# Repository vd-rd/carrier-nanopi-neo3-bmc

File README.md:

# NanoPi Neo 3 Carrier board

This board is designed to enhance the FriendlyElec NanoPi Neo 3 board with features suitable for a "server" style deployment. It uses a ESP32 as a BMC.

Features provided:
 - RTC clock 
 - Wired Ethernet interface
 - Gated power supply

## Motivation

Most SBC platforms lack the features needed for a rack style deployment where you can power cycle the board or get a remote console to debug what went wrong.
The ESP32 uC is fairly popular, but the reason behind selecting it to act as a BMC is that is one of the cheapest uCs equipped with a Ethernet PHY.

## Hardware overview
 (Diagram)

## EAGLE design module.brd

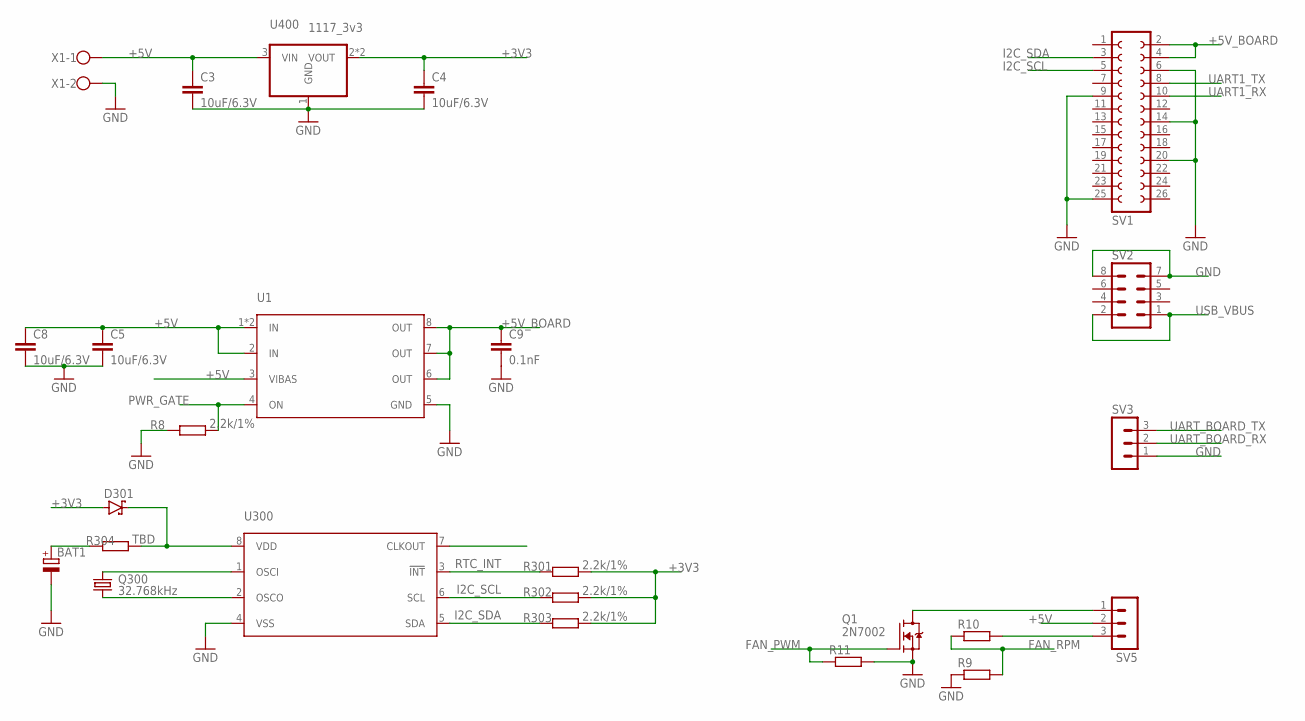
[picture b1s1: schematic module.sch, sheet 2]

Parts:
BAT1: DCK-3R3E224U-E; 621
C3, C4: 10uF/6.3V; C1206
C5, C8: 10uF/6.3V; C0603
C9: 0.1nF; C0603
D301: NSR0320; SOD323
Q1: 2N7002; SOT95P240X110-3
Q300: 32.768kHz; 3215
R8, R301, R302, R303: 2.2k/1%; R0603
R9, R10, R11: R-EU_R0603; R0603
R304: TBD; R0603
SV1: FE13-2
SV2: MA04-2
SV3: MA03-1FEMALE; MA03-1
SV5: MA03-1
U1: DML10M8LDS; SON65P300X300X80-9T160X240N
U300: PCF85063ATT; SOP65P490X110-8N
U400: 1117_3v3; SOT230P700X180-4
X1: W237-102; EBBA

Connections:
+3V3: C4.1, D301.A, R301.2, R302.2, R303.2, U400.2 (VOUT), U400.4 (VOUT); also elsewhere on the board
+5V: C3.1, C5.1, C8.1, SV5.2, U1.1 (IN), U1.2 (IN), U1.3 (VIBAS), U1.9 (IN), U400.3 (VIN), X1.1
+5V_BOARD: C9.1, SV1.2, SV1.4, U1.6 (OUT), U1.7 (OUT), U1.8 (OUT)
FAN_PWM: Q1.1 (G), R11.1; also elsewhere on the board
FAN_RPM: R9.2, R10.1; also elsewhere on the board
GND: BAT1.-, C3.2, C4.2, C5.2, C8.2, C9.2, Q1.2 (S), R8.1, R9.1, R11.2, SV1.6, SV1.9, SV1.14, SV1.20, SV1.25, SV2.7, SV2.8, SV3.1, U1.5 (GND), U300.4 (VSS), U400.1 (GND), X1.2; also elsewhere on the board
I2C_SCL: R302.1, SV1.5, U300.6 (SCL); also elsewhere on the board
I2C_SDA: R303.1, SV1.3, U300.5 (SDA); also elsewhere on the board
unnamed: Q1.3 (D), SV5.1
unnamed: R10.2, SV5.3
unnamed: Q300.1, U300.2 (OSCO)
unnamed: Q300.2, U300.1 (OSCI)
unnamed: BAT1.+, R304.1
unnamed: D301.K (C), R304.2, U300.8 (VDD)
PWR_GATE: R8.2, U1.4 (ON); also elsewhere on the board
RTC_INT: R301.1, U300.3 (!INT)
UART1_RX: SV1.10
UART1_TX: SV1.8
UART_BOARD_RX: SV3.2; also elsewhere on the board
UART_BOARD_TX: SV3.3; also elsewhere on the board
USB_VBUS: SV2.1, SV2.2

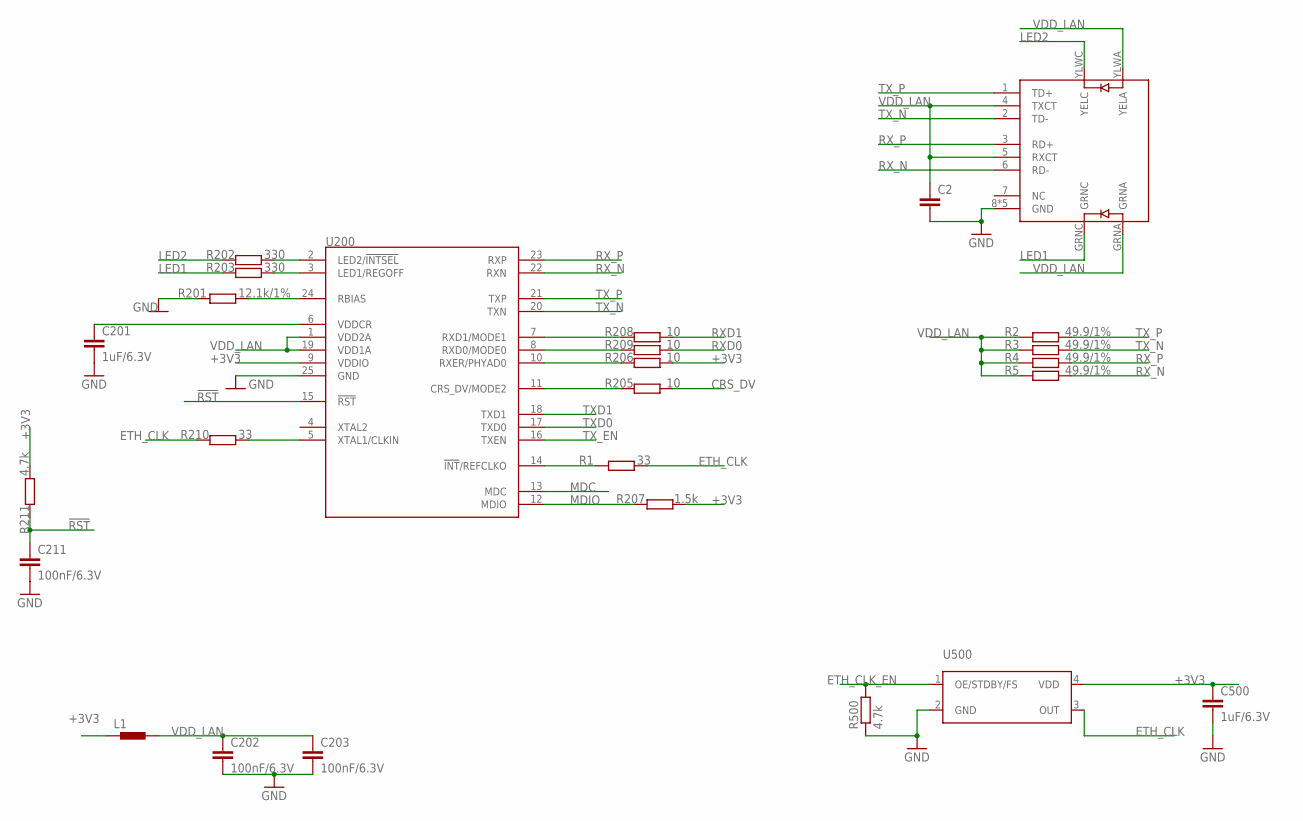
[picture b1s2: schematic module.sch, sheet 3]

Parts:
C2: C-EUC0603; C0603
C201, C500: 1uF/6.3V; C0603
C202, C203, C211: 100nF/6.3V; C0603
J1: ARJM11X1009XXXXX; LAYOUT1-HORIZ-LEDS
L1: FER-0603; FER0603
R1, R210: 33; R0603
R2, R3, R4, R5: 49.9/1%; R0603
R201: 12.1k/1%; R0603
R202, R203: 330; R0603
R205, R206, R208, R209: 10; R0603
R207: 1.5k; R0603
R211, R500: 4.7k; R0603
U200: LAN8720A; QFN50P400X400X100-25T250N
U500: DSC61XXC; DIODFN250X200X89-4N

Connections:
!RST: C211.1, R211.1, U200.15 (!RST)
+3V3: C500.1, L1.1, R206.2, R207.2, R211.2, U200.9 (VDDIO), U500.4 (VDD); also elsewhere on the board
CRS_DV: R205.2; also elsewhere on the board
ETH_CLK: R1.2, R210.1, U500.3 (OUT); also elsewhere on the board
ETH_CLK_EN: R500.2, U500.1 (OE/STDBY/FS); also elsewhere on the board
GND: C2.2, C201.2, C202.2, C203.2, C211.2, C500.2, J1.8 (GND), J1.P$1 (GND), J1.P$2 (GND), J1.P$3 (GND), J1.P$4 (GND), R201.1, R500.1, U200.25 (GND), U500.2 (GND); also elsewhere on the board
LED1: J1.GRNC, R203.1
LED2: J1.YLWC (YELC), R202.1
MDC: U200.13 (MDC); also elsewhere on the board
MDIO: R207.1, U200.12 (MDIO); also elsewhere on the board
unnamed: R208.1, U200.7 (RXD1/MODE1)
unnamed: R210.2, U200.5 (XTAL1/CLKIN)
unnamed: C201.1, U200.6 (VDDCR)
unnamed: R202.2, U200.2 (LED2/!INTSEL)
unnamed: R203.2, U200.3 (LED1/REGOFF)
unnamed: R209.1, U200.8 (RXD0/MODE0)
unnamed: R201.2, U200.24 (RBIAS)
unnamed: R206.1, U200.10 (RXER/PHYAD0)
unnamed: R205.1, U200.11 (CRS_DV/MODE2)
unnamed: R1.1, U200.14 (!INT!/REFCLKO)
RXD0: R209.2; also elsewhere on the board
RXD1: R208.2; also elsewhere on the board
RX_N: J1.6 (RD-), R5.2, U200.22 (RXN)
RX_P: J1.3 (RD+), R4.2, U200.23 (RXP)
TXD0: U200.17 (TXD0); also elsewhere on the board
TXD1: U200.18 (TXD1); also elsewhere on the board
TX_EN: U200.16 (TXEN); also elsewhere on the board
TX_N: J1.2 (TD-), R3.2, U200.20 (TXN)
TX_P: J1.1 (TD+), R2.2, U200.21 (TXP)
VDD_LAN: C2.1, C202.1, C203.1, J1.4 (TXCT), J1.5 (RXCT), J1.GRNA, J1.YLWA (YELA), L1.2, R2.1, R3.1, R4.1, R5.1, U200.1 (VDD2A), U200.19 (VDD1A)

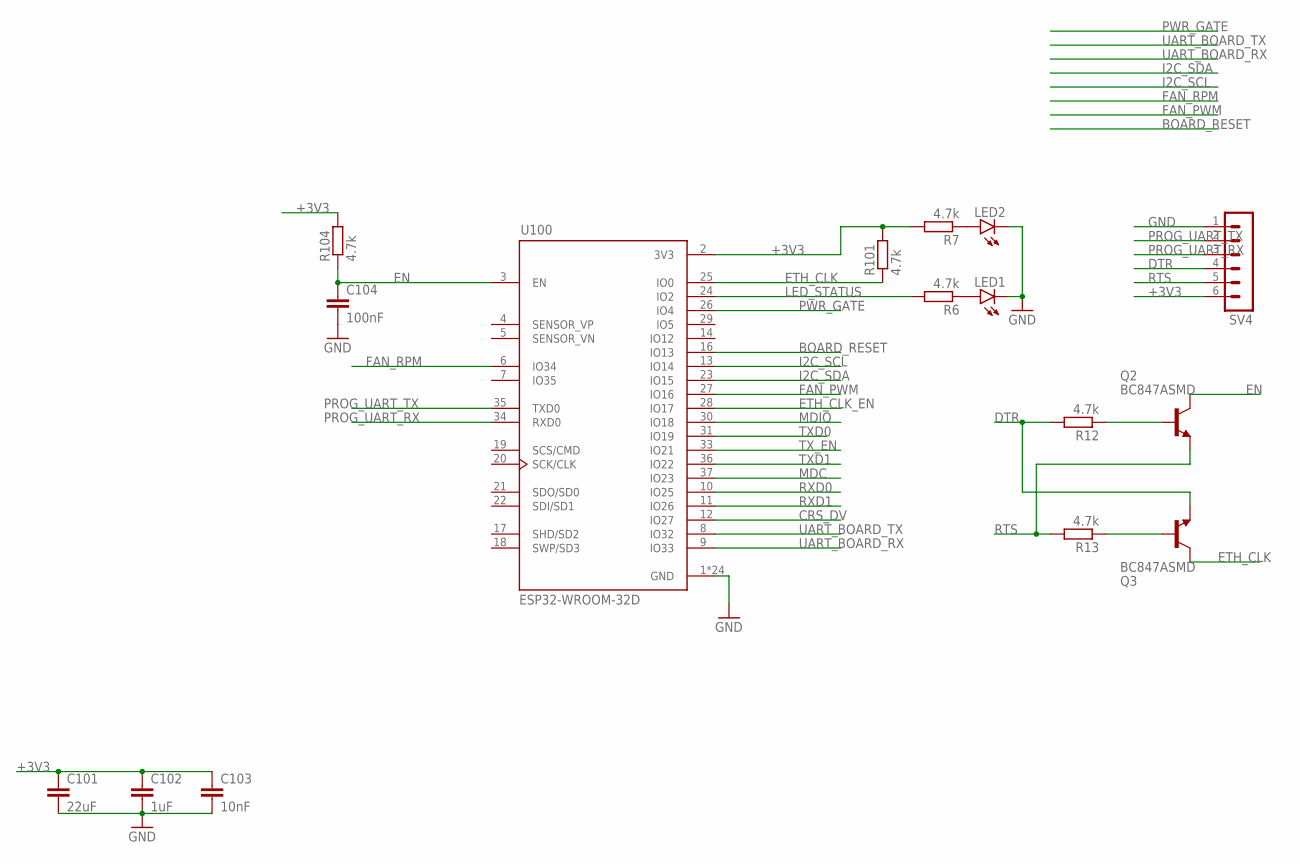
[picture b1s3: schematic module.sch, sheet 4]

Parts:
C101: 22uF; C1206
C102: 1uF; C0603
C103: 10nF; C0603
C104: 100nF; C0603
LED1, LED2: LEDCHIP-LED0805; CHIP-LED0805
Q2, Q3: BC847ASMD; SOT23
R6, R7, R12, R13, R101, R104: 4.7k; R0603
SV4: CONN-1X6; MA06-1
U100: ESP32-WROOM-32D; MODULE_ESP32-WROOM-32D

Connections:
+3V3: C101.1, C102.1, C103.1, R7.2, R101.2, R104.2, SV4.6, U100.2 (3V3); also elsewhere on the board
BOARD_RESET: U100.16 (IO13)
CRS_DV: U100.12 (IO27); also elsewhere on the board
DTR: Q3.2 (E), R12.2, SV4.4
EN: C104.1, Q2.3 (C), R104.1, U100.3 (EN)
ETH_CLK: Q3.3 (C), R101.1, U100.25 (IO0); also elsewhere on the board
ETH_CLK_EN: U100.28 (IO17); also elsewhere on the board
FAN_PWM: U100.27 (IO16); also elsewhere on the board
FAN_RPM: U100.6 (IO34); also elsewhere on the board
GND: C101.2, C102.2, C103.2, C104.2, LED1.C, LED2.C, SV4.1, U100.1 (GND), U100.15 (GND), U100.38 (GND), U100.39_1 (GND), U100.39_2 (GND), U100.39_3 (GND), U100.39_4 (GND), U100.39_5 (GND), U100.39_6 (GND), U100.39_7 (GND), U100.39_8 (GND), U100.39_9 (GND), U100.39_10 (GND), U100.39_11 (GND), U100.39_12 (GND), U100.39_13 (GND), U100.39_14 (GND), U100.39_15 (GND), U100.39_16 (GND), U100.39_17 (GND), U100.39_18 (GND), U100.39_19 (GND), U100.39_20 (GND), U100.39_21 (GND); also elsewhere on the board
I2C_SCL: U100.13 (IO14); also elsewhere on the board
I2C_SDA: U100.23 (IO15); also elsewhere on the board
LED_STATUS: R6.2, U100.24 (IO2)
MDC: U100.37 (IO23); also elsewhere on the board
MDIO: U100.30 (IO18); also elsewhere on the board
unnamed: LED1.A, R6.1
unnamed: LED2.A, R7.1
unnamed: Q2.1 (B), R12.1
unnamed: Q3.1 (B), R13.1
PROG_UART_RX: SV4.3, U100.34 (RXD0)
PROG_UART_TX: SV4.2, U100.35 (TXD0)
PWR_GATE: U100.26 (IO4); also elsewhere on the board
RTS: Q2.2 (E), R13.2, SV4.5
RXD0: U100.10 (IO25); also elsewhere on the board
RXD1: U100.11 (IO26); also elsewhere on the board
TXD0: U100.31 (IO19); also elsewhere on the board
TXD1: U100.36 (IO22); also elsewhere on the board
TX_EN: U100.33 (IO21); also elsewhere on the board
UART_BOARD_RX: U100.9 (IO33); also elsewhere on the board
UART_BOARD_TX: U100.8 (IO32); also elsewhere on the board

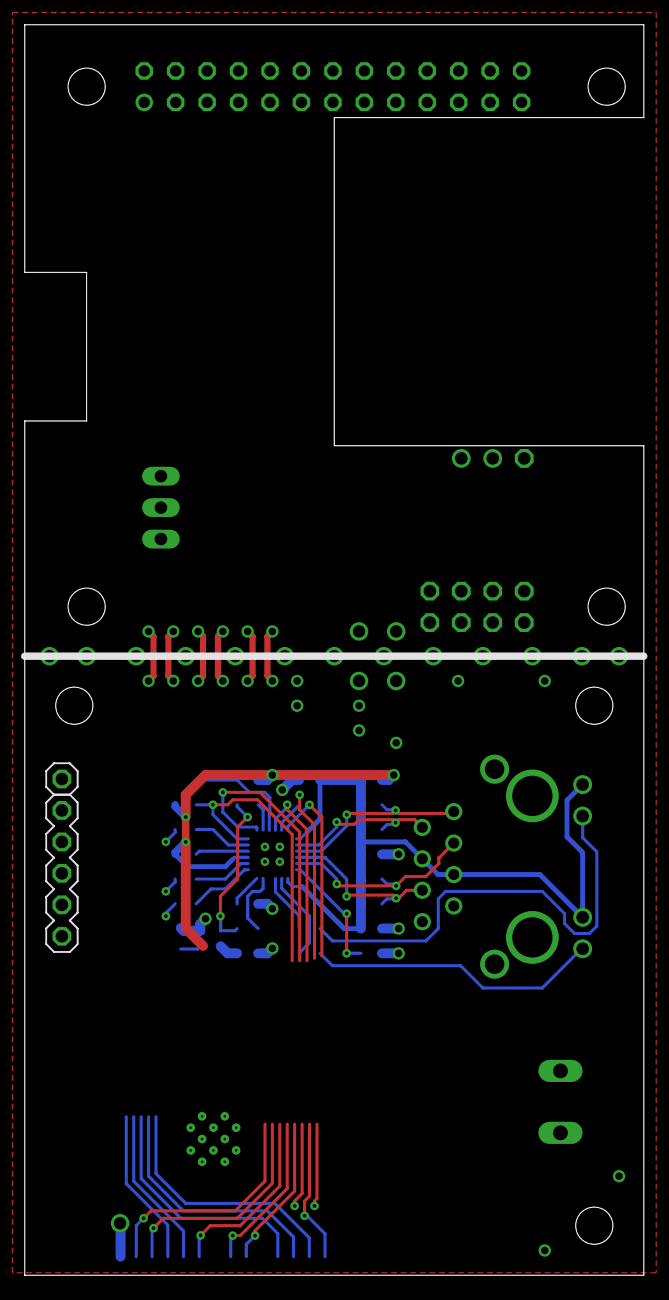
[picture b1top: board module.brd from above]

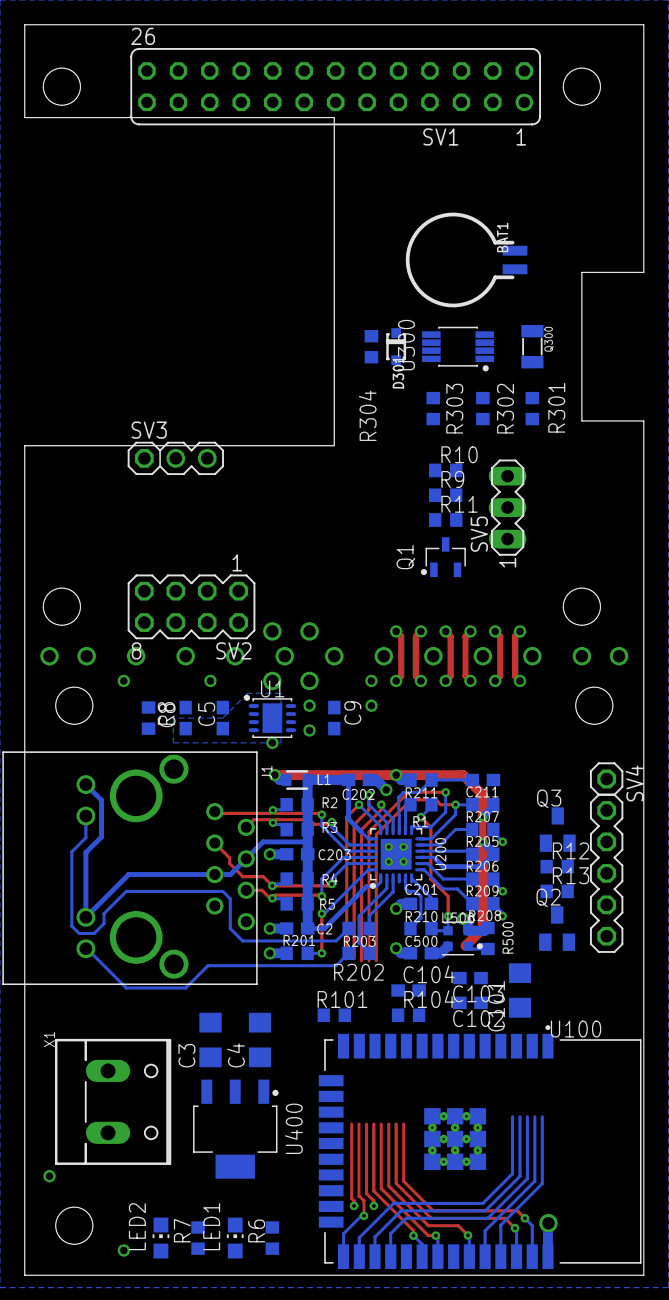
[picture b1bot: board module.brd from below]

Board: 2 copper layers, 50.0 x 101.0 mm, 67 parts (67 on the bottom side), 57 nets.

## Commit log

2020-12-05 project: add initial board
2020-12-08 project: add rtc
2020-12-08 project: add ldo
2020-12-29 project: change rj45 with integrated magnetics
2020-12-29 schematic: complete ethernet phy
2020-12-29 layout: improve component placement
2020-12-30 project: update readme
2020-12-30 Update TOC
2020-12-31 layout: more routing
2020-12-31 project: relayout
2021-01-02 schematic: add signal section
2021-01-03 board: add program header
2021-01-03 project: add fan controller
2021-01-03 project: route some signals
